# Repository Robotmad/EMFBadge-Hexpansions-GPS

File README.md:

# 📡 GPS Hexpansion for Tildagon Badge

A GPS Hexpansion module and basic software implementation for the Tildagon badge.

This project provides a working foundation for adding location awareness to badge applications — including hardware integration, UART communication, and NMEA parsing.

Designed for experimentation, hacking, and building more advanced location-based features.

They are available to buy here: https://themachineshop.uk/products/gps-hexpansion/

---

## ✨ Overview

This repository contains:

* ⚙️ Hardware files built in KiCAD
* 📡 UART-based communication with a GPS module
* 🧠 Basic NMEA parsing (RMC / GGA)
* 🖥️ Minimal software to extract and use position data
* 📷 Images of the board

It’s intended as a **starting point** for developing GPS-enabled badge apps.

---

## 🖼️ Hardware

---

## 🔌 Hardware Details

* Compatible with the EMF2026 Tildagon Badge
* L80RE-M37 GPS module with built-in patch antenna
* External antenna connector with automatic switch over
* M24C16-RMN6TP EEPROM
* Red and Yellow LEDs

## ⚙️ Software

The software demonstrates:

* Reading serial data from the GPS module
* Parsing NMEA sentences (`$GNRMC`, `$GPGGA`)
* Extracting:

  * Latitude
  * Longitude
  * Fix status

This provides a clean base layer for any GPS-driven feature.

---

## 🧠 How It Works

1. GPS module outputs NMEA strings over UART
2. Badge reads serial stream
3. Valid sentences are identified
4. Data is parsed into usable values
5. Position data becomes available to your application
6. LED D1 is lit when there is a valid fix
---

## 🚀 Getting Started

```bash
git clone https://github.com/TechCabin/EMFBadge-Hexpansions-GPS.git
```

1. Flash MicroPython to your badge via mpremote
2. Copy project files to the device
3. Connect the GPS module via UART
4. Power on the badge
5. Wait for a valid GPS fix

---

## ⚠️ Notes

* Outdoor use significantly improves performance
* First fix can take 30–60 seconds (cold start)

---

## 🛣️ TODO

* [ ] Improve NMEA parser robustness
* [ ] Add support for additional sentence types
* [ ] Abstract GPS into a reusable module/class
* [ ] Add example applications (mapping, tracking, etc.)
* [ ] Add signal quality / satellite info

---

## 🔧 Future Ideas

* Real-time mapping
* Etch-a-Sktech app
* Geofencing features
* Time synchronisation from GPS
* Capture the Flag game
* Find a Friend app

---

## 🤝 Contributing

Contributions welcome — especially if you build something cool on top of this.

---

## 🙌 Acknowledgements

* EMF Camp
* Tildagon badge creators
* Open-source GPS/NMEA documentation

---

## 📜 License

MIT

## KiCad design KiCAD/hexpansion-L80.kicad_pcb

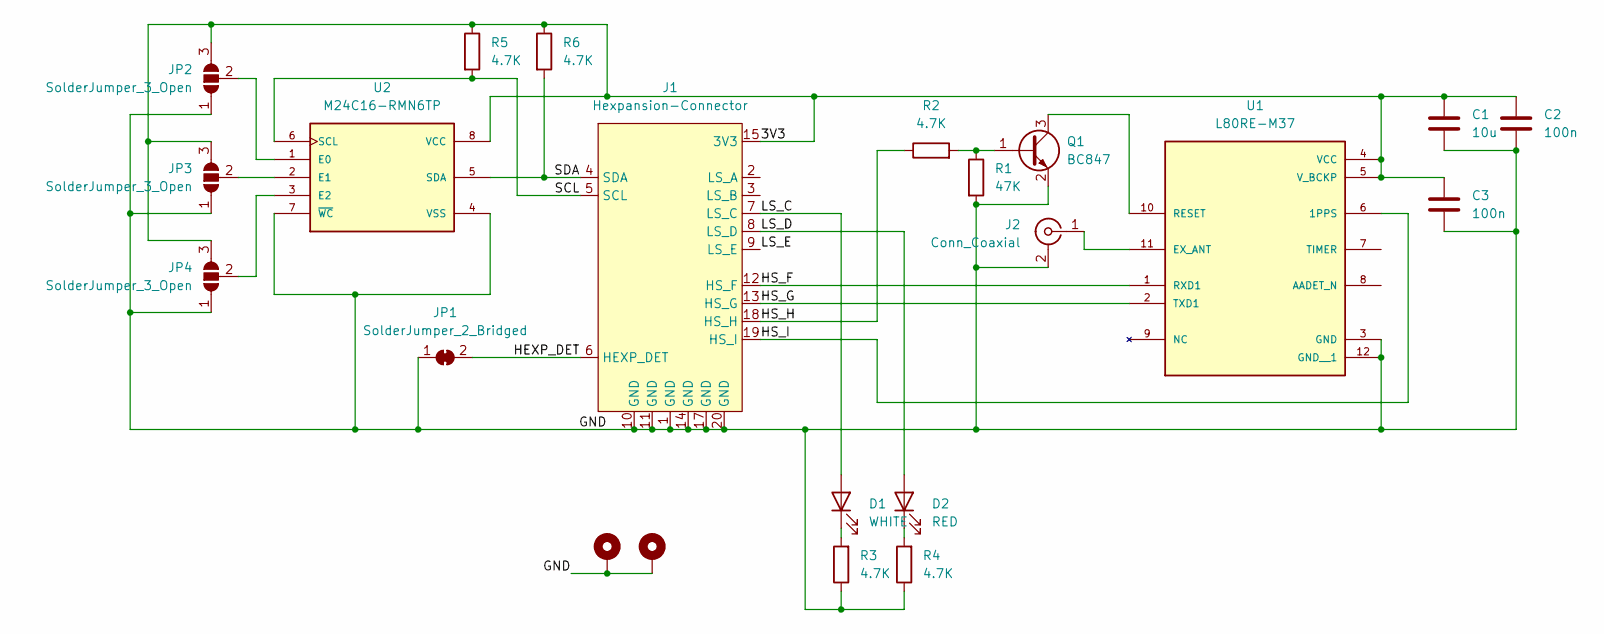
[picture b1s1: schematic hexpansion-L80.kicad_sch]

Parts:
C1: 10u; C_0402_1005Metric
C2, C3: 100n; C_0402_1005Metric
D1: WHITE; LED_0603_1608Metric
D2: RED; LED_0603_1608Metric
H1, H2: MountingHole_Pad; MountingHole_2.2mm_M2_Pad_Via
J1: Hexpansion-Connector; hexpansion-edge-connector
J2: Conn_Coaxial; U.FL_Hirose_U.FL-R-SMT-1_Vertical
JP1: SolderJumper_2_Bridged; SolderJumper-2_P1.3mm_Bridged_RoundedPad1.0x1.5mm
JP2, JP3, JP4: SolderJumper_3_Open
Q1: BC847; SOT-23
R1: 47K; R_0402_1005Metric
R2, R3, R4, R5, R6: 4.7K; R_0402_1005Metric
U1: L80RE-M37; XCVR_L80RE-M37; PARTREV v1.4
U2: M24C16-RMN6TP; SOIC127P600X175-8N

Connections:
/3V3: C1.1, C2.1, C3.1, J1.15 (3V3), J1.16 (3V3), JP2.3 (B), JP3.3 (B), JP4.3 (B), R5.1, R6.1, U1.4 (VCC), U1.5 (V_BCKP), U2.8 (VCC)
/GND: C1.2, C2.2, C3.2, H1.1, H2.1, J1.1 (GND), J1.10 (GND), J1.11 (GND), J1.14 (GND), J1.17 (GND), J1.20 (GND), J2.2 (Ext), JP1.1 (A), JP2.1 (A), JP3.1 (A), JP4.1 (A), Q1.2 (E), R1.2, R3.1, R4.1, U1.3 (GND), U1.12 (GND__1), U2.4 (VSS), U2.7 (~WC)
/HEXP_DET: J1.6 (HEXP_DET), JP1.2 (B)
/HS_F: J1.12 (HS_F), U1.1 (RXD1)
/HS_G: J1.13 (HS_G), U1.2 (TXD1)
/HS_H: J1.18 (HS_H), R2.1
/HS_I: J1.19 (HS_I), U1.6 (1PPS)
/LS_C: D1.2 (A), J1.7 (LS_C)
/LS_D: D2.2 (A), J1.8 (LS_D)
/LS_E: J1.9 (LS_E)
/SCL: J1.5 (SCL), R5.2, U2.6 (SCL)
/SDA: J1.4 (SDA), R6.2, U2.5 (SDA)
unnamed: D1.1 (K), R3.2
unnamed: D2.1 (K), R4.2
unnamed: J2.1 (In), U1.11 (EX_ANT)
unnamed: JP2.2 (C), U2.1 (E0)
unnamed: JP3.2 (C), U2.2 (E1)
unnamed: JP4.2 (C), U2.3 (E2)
unnamed: Q1.1 (B), R1.1, R2.2
unnamed: Q1.3 (C), U1.10 (RESET)

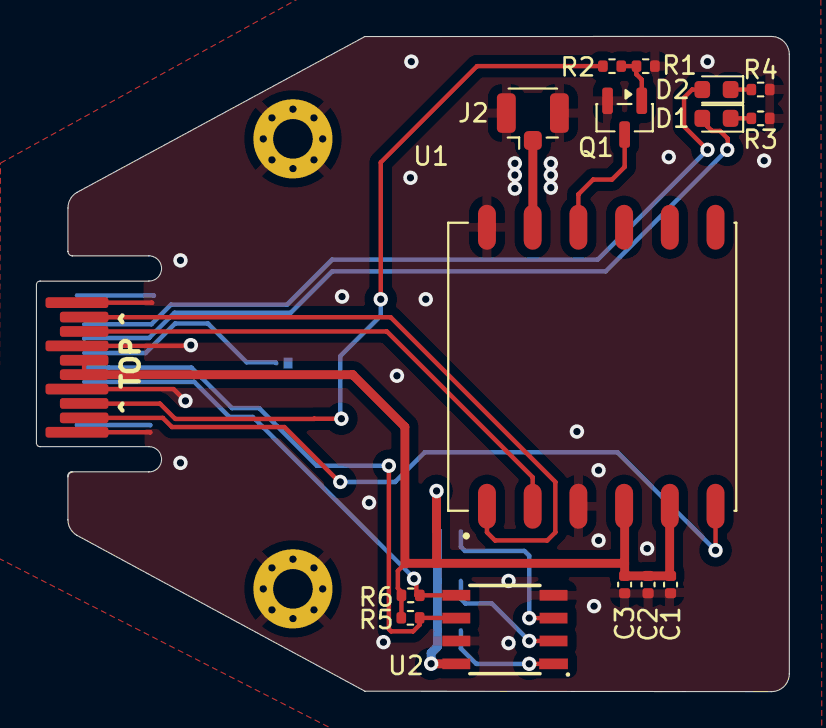
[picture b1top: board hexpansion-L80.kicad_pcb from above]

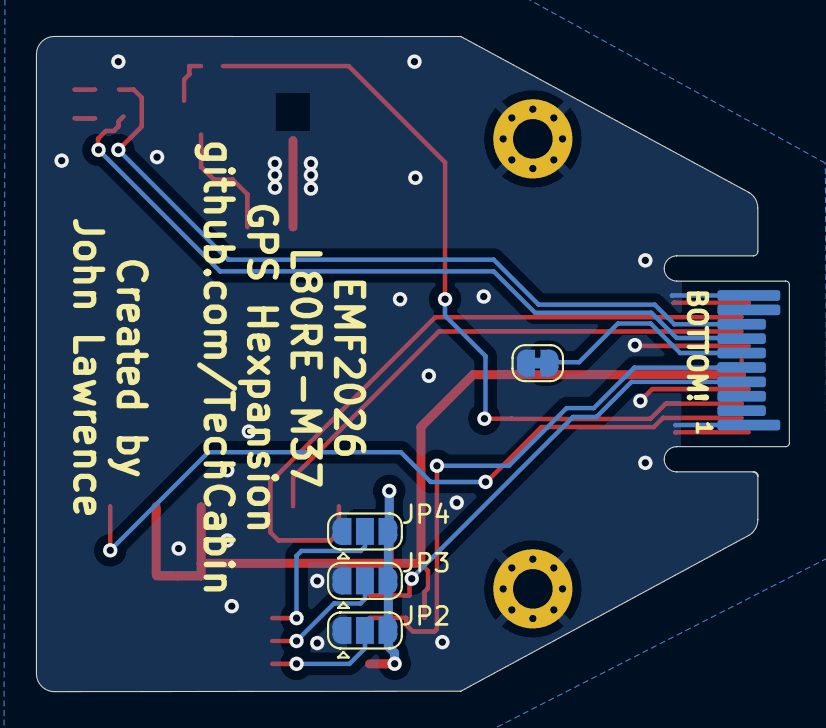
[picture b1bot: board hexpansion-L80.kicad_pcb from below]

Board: 2 copper layers, 41.8 x 36.4 mm, 22 parts (4 on the bottom side), 19 nets.

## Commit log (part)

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2026-03-30 initial upload
2026-04-06 uploading Software
2026-04-07 Adding images of finished board
2026-04-09 changed images
2026-04-10 Rename IMG_1443.jpeg to GPS-With-Badge
2026-04-10 Rename GPS-TOP.jpeg to GPS-Top.jpeg
2026-04-20 automatic hexpansion detection
2026-05-02 Refactor version handling in L80KApp class
    Moved VERSION into the L80KApp class and removed get_version method.
2026-05-03 Swap TX and RX pin definitions for GPS module
2026-05-25 rotated LEDs, fixed footprint sizing and regenerated production files
2026-05-25 rotated LEDs, fixed footprint sizing and rebuilt production files
2026-05-25 updated images
2026-05-25 corrected image links
2026-06-01 Change purchasing link
2026-06-07 new GPS basic app utilising the EEPROM code
2026-06-07 adding EEPROM files
2026-06-07 adding tildagon.toml
2026-06-07 moved tildagon.toml and added .gitattributes file
2026-06-07 added .DS_Store to .gitattributes file
2026-06-07 added .gitignore and metadata.json to .gitattributes file
2026-06-07 added EEPROM directory to .gitattributes file
2026-06-07 added export-ignore to EEPROM in .gitattributes file
2026-06-21 D1 indicates when fix is valid
    Initialise LS pin for D1 and set it active (high) when there is a valid fix.
    support deinit() function to tidy up use of resources when hexpansion removed as per https://github.com/emfcamp/badge-2024-software/pull/328
2026-06-21 Update README with LED indicator and TODO changes
    Added note about LED D1 indicating a valid fix and removed a TODO item regarding auto-detection of hexpansion port.
2026-06-24 check availability of UART resource
